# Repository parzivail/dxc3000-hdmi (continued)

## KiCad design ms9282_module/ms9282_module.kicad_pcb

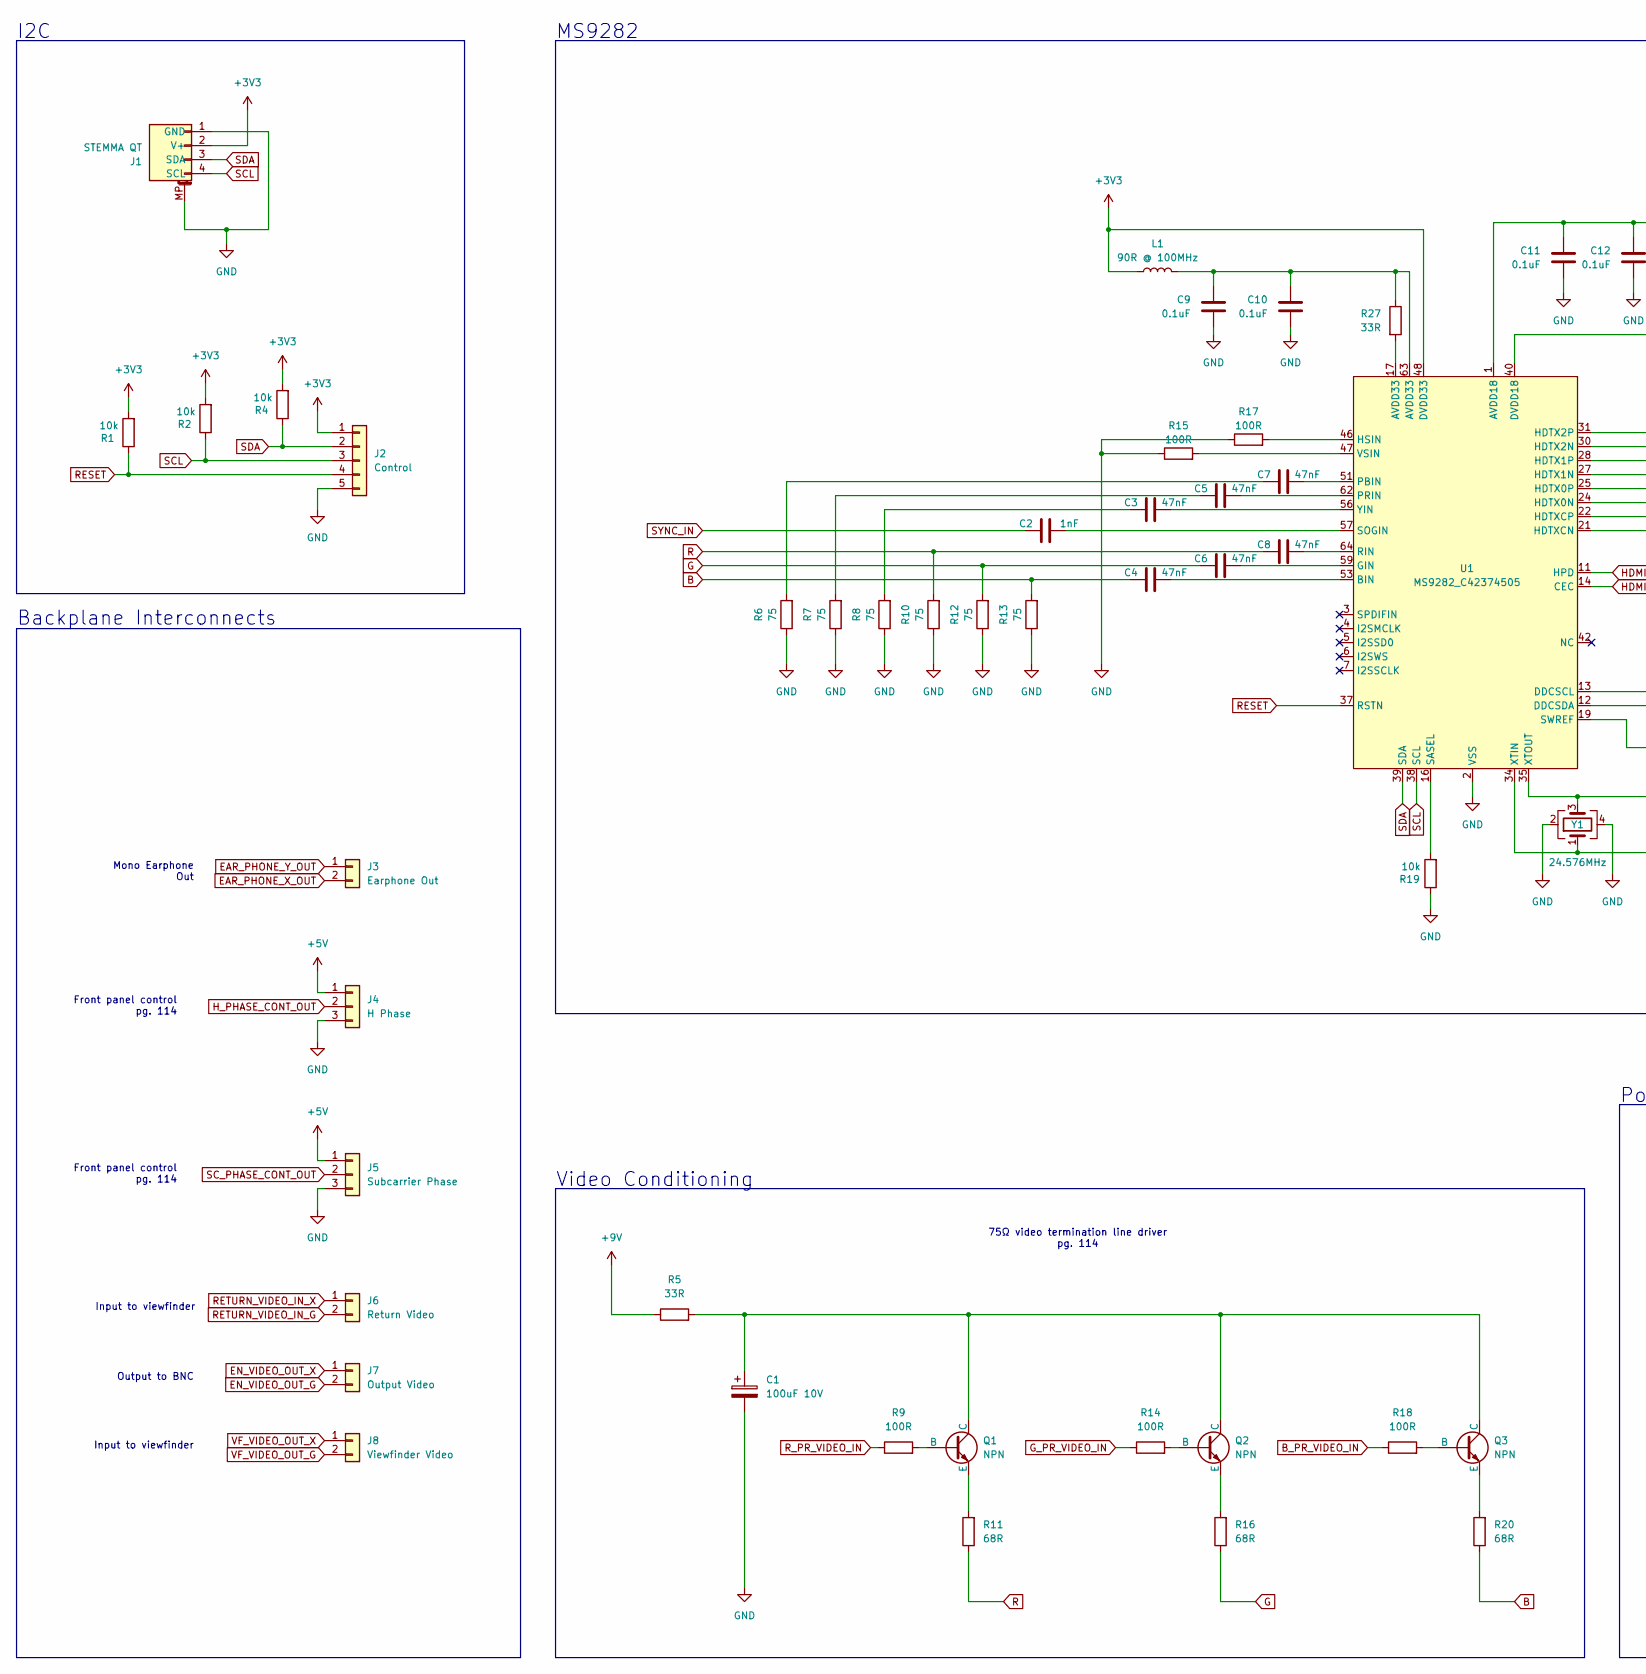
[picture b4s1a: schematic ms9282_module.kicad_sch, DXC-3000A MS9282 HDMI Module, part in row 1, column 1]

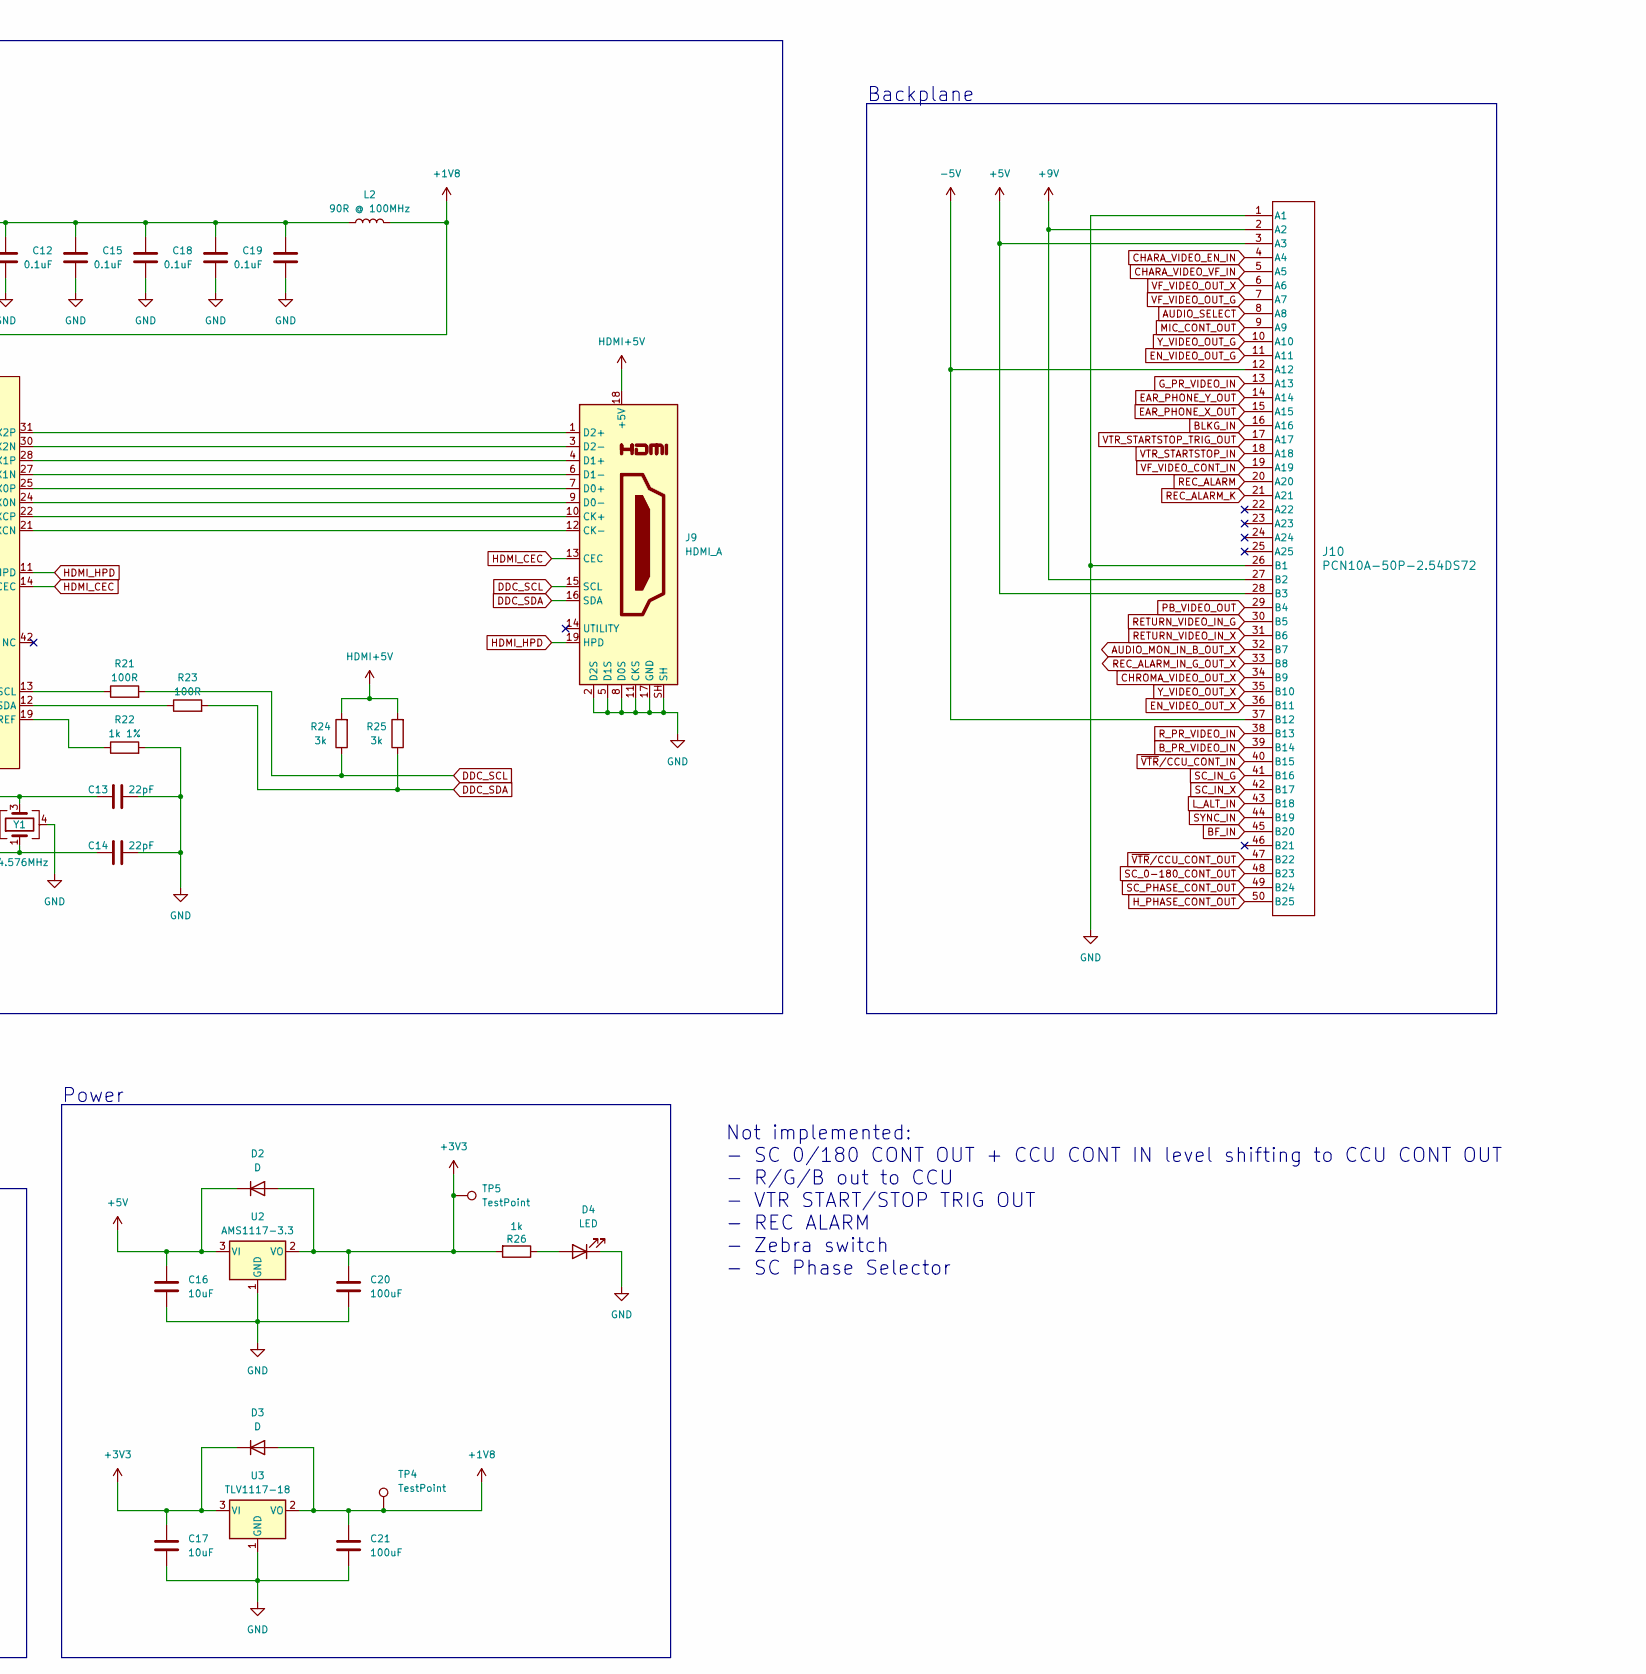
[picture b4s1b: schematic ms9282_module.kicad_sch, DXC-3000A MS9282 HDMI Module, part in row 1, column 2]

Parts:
C1: 100uF 10V; C_1206_3216Metric; LCSC Part C15008
C2: 1nF; C_0402_1005Metric; LCSC Part C1523
C3, C4, C5, C6, C7, C8: 47nF; C_0402_1005Metric; LCSC Part C307434
C9, C10, C11, C12, C15, C18, C19: 0.1uF; C_0402_1005Metric; LCSC Part C1525
C13, C14: 22pF; C_0402_1005Metric; LCSC Part C1555
C16, C17: 10uF; C_0402_1005Metric; LCSC Part C15525
C20, C21: 100uF; C_1206_3216Metric; LCSC Part C15008
D2, D3: D; D_SOD-123F; LCSC Part C64898
D4: LED; LED_0603_1608Metric; LCSC Part C2286
J1: STEMMA QT; JST_SH_SM04B-SRSS-TB_1x04-1MP_P1.00mm_Horizontal; LCSC Part C160404
J2: Control; PinHeader_1x05_P2.54mm_Horizontal
J3: Earphone Out; PinHeader_1x02_P2.54mm_Horizontal
J4: H Phase; PinHeader_1x03_P2.54mm_Horizontal
J5: Subcarrier Phase; PinHeader_1x03_P2.54mm_Horizontal
J6: Return Video; PinHeader_1x02_P2.54mm_Horizontal
J7: Output Video; PinHeader_1x02_P2.54mm_Horizontal
J8: Viewfinder Video; PinHeader_1x02_P2.54mm_Horizontal
J9: HDMI_A; HDMI_A_Molex_208658-1001_Horizontal; LCSC Part C2858275
J10: PCN10A-50P-2.54DS72; CONN_PCN10A-50P_HIR
L1, L2: 90R @ 100MHz; L_0805_2012Metric; LCSC Part C1015
Q1, Q2, Q3: NPN; SOT-23; LCSC Part C27829
R1, R2, R4, R19: 10k; R_0402_1005Metric; LCSC Part C25744
R5, R27: 33R; R_0402_1005Metric; LCSC Part C25105
R6, R7, R8, R10, R12, R13: 75; R_0402_1005Metric; LCSC Part C25133
R9, R14, R15, R17, R18, R21, R23: 100R; R_0402_1005Metric; LCSC Part C25076
R11, R16, R20: 68R; R_0603_1608Metric; LCSC Part C27592
R22: 1k 1%; R_0402_1005Metric; LCSC Part C11702
R24, R25: 3k; R_0402_1005Metric; LCSC Part C25890
R26: 1k; R_0402_1005Metric; LCSC Part C11702
TP4, TP5: TestPoint; TestPoint_Pad_D1.0mm
U1: MS9282_C42374505; LQFP-64_L10.0-W10.0-P0.50-LS12.0-BL; LCSC Part C42374505
U2: AMS1117-3.3; SOT-223-3_TabPin2; LCSC Part C6186
U3: TLV1117-18; SOT-223-3_TabPin2; LCSC Part C2862410
Y1: 24.576MHz; Crystal_SMD_3225-4Pin_3.2x2.5mm; LCSC Part C654993

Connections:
+1V8: C21.1, D3.2 (A), L2.2, TP4.1, U1.9 (DVDD18), U1.40 (DVDD18), U3.2 (VO)
+3V3: C17.1, C20.1, D2.2 (A), D3.1 (K), J1.2 (V+), J2.1, L1.1, R1.2, R2.2, R4.2, R26.2, TP5.1, U1.15 (DVDD33), U1.33 (DVDD33), U1.48 (DVDD33), U2.2 (VO), U3.3 (VI)
+5V: C16.1, D2.1 (K), J4.1, J5.1, J10.3 (A3), J10.28 (B3), U2.3 (VI)
+9V: J10.2 (A2), J10.27 (B2), R5.1
-5V: J10.12 (A12), J10.37 (B12)
AUDIO_MON_IN_B_OUT_X: J10.32 (B7)
AUDIO_SELECT: J10.8 (A8)
B: C4.2, R13.2, R20.1
BF_IN: J10.45 (B20)
BLKG_IN: J10.16 (A16)
B_PR_VIDEO_IN: J10.39 (B14), R18.1
CHARA_VIDEO_EN_IN: J10.4 (A4)
CHARA_VIDEO_VF_IN: J10.5 (A5)
CHROMA_VIDEO_OUT_X: J10.34 (B9)
DDC_SCL: J9.15 (SCL), R21.2, R24.1
DDC_SDA: J9.16 (SDA), R23.2, R25.1
EAR_PHONE_X_OUT: J3.2, J10.15 (A15)
EAR_PHONE_Y_OUT: J3.1, J10.14 (A14)
EN_VIDEO_OUT_G: J7.2, J10.11 (A11)
EN_VIDEO_OUT_X: J7.1, J10.36 (B11)
G: C6.2, R12.2, R16.1
GND: C1.2, C9.2, C10.2, C11.2, C12.2, C13.1, C14.1, C15.2, C16.2, C17.2, C18.2, C19.2, C20.2, C21.2, D4.1 (K), J1.1 (GND), J1.MP, J2.5, J4.3, J5.3, J9.2 (D2S), J9.5 (D1S), J9.8 (D0S), J9.11 (CKS), J9.17 (GND), J9.SH, J10.1 (A1), J10.26 (B1), R6.1, R7.1, R8.1, R10.1, R12.1, R13.1, R15.1, R17.1, R19.1, R22.2, U1.2 (VSS), U1.8 (VSS), U1.10 (VSS), U1.18 (VSS), U1.20 (VSS), U1.26 (VSS), U1.32 (VSS), U1.36 (VSS), U1.41 (VSS), U1.45 (VSS), U1.50 (VSS), U1.54 (VSS), U1.60 (VSS), U2.1 (GND), U3.1 (GND), Y1.2, Y1.4
G_PR_VIDEO_IN: J10.13 (A13), R14.1
HDMI+5V: J9.18 (+5V), R24.2, R25.2
HDMI_CEC: J9.13 (CEC), U1.14 (CEC)
HDMI_HPD: J9.19 (HPD), U1.11 (HPD)
H_PHASE_CONT_OUT: J4.2, J10.50 (B25)
L_ALT_IN: J10.43 (B18)
MIC_CONT_OUT: J10.9 (A9)
unnamed: C3.2, R8.2
unnamed: C5.2, R7.2
unnamed: C7.2, R6.2
unnamed: C9.1, C10.1, L1.2, R27.1, U1.49 (AVDD33), U1.52 (AVDD33), U1.58 (AVDD33), U1.63 (AVDD33)
unnamed: C11.1, C12.1, C15.1, C18.1, C19.1, L2.1, U1.1 (AVDD18), U1.23 (AVDD18), U1.29 (AVDD18), U1.55 (AVDD18), U1.61 (AVDD18)
unnamed: D4.2 (A), R26.1
unnamed: J9.10 (CK+), U1.22 (HDTXCP)
unnamed: J9.12 (CK-), U1.21 (HDTXCN)
unnamed: J9.7 (D0+), U1.25 (HDTX0P)
unnamed: J9.9 (D0-), U1.24 (HDTX0N)
unnamed: J9.4 (D1+), U1.28 (HDTX1P)
unnamed: J9.6 (D1-), U1.27 (HDTX1N)
unnamed: J9.1 (D2+), U1.31 (HDTX2P)
unnamed: J9.3 (D2-), U1.30 (HDTX2N)
unnamed: Q1.1 (B), R9.2
unnamed: C1.1, Q1.3 (C), Q2.3 (C), Q3.3 (C), R5.2
unnamed: Q1.2 (E), R11.2
unnamed: Q2.1 (B), R14.2
unnamed: Q2.2 (E), R16.2
unnamed: Q3.1 (B), R18.2
unnamed: Q3.2 (E), R20.2
unnamed: R27.2, U1.17 (AVDD33)
unnamed: C4.1, U1.53 (BIN)
unnamed: R21.1, U1.13 (DDCSCL)
unnamed: R23.1, U1.12 (DDCSDA)
unnamed: C6.1, U1.59 (GIN)
unnamed: R17.2, U1.46 (HSIN)
unnamed: C7.1, U1.51 (PBIN)
unnamed: C5.1, U1.62 (PRIN)
unnamed: C8.1, U1.64 (RIN)
unnamed: R19.2, U1.16 (SASEL)
unnamed: C2.1, U1.57 (SOGIN)
unnamed: R22.1, U1.19 (SWREF)
unnamed: R15.2, U1.47 (VSIN)
unnamed: C14.2, U1.34 (XTIN), Y1.1
unnamed: C13.2, U1.35 (XTOUT), Y1.3
unnamed: C3.1, U1.56 (YIN)
PB_VIDEO_OUT: J10.29 (B4)
R: C8.2, R10.2, R11.1
REC_ALARM: J10.20 (A20)
REC_ALARM_IN_G_OUT_X: J10.33 (B8)
REC_ALARM_K: J10.21 (A21)
RESET: J2.4, R1.1, U1.37 (RSTN)
RETURN_VIDEO_IN_G: J6.2, J10.30 (B5)
RETURN_VIDEO_IN_X: J6.1, J10.31 (B6)
R_PR_VIDEO_IN: J10.38 (B13), R9.1
SCL: J1.4 (SCL), J2.3, R2.1, U1.38 (SCL)
SC_0-180_CONT_OUT: J10.48 (B23)
SC_IN_G: J10.41 (B16)
SC_IN_X: J10.42 (B17)
SC_PHASE_CONT_OUT: J5.2, J10.49 (B24)
SDA: J1.3 (SDA), J2.2, R4.1, U1.39 (SDA)
SYNC_IN: C2.2, J10.44 (B19)
VF_VIDEO_CONT_IN: J10.19 (A19)
VF_VIDEO_OUT_G: J8.2, J10.7 (A7)
VF_VIDEO_OUT_X: J8.1, J10.6 (A6)
VTR_STARTSTOP_IN: J10.18 (A18)
VTR_STARTSTOP_TRIG_OUT: J10.17 (A17)
Y_VIDEO_OUT_G: J10.10 (A10)
Y_VIDEO_OUT_X: J10.35 (B10)
~VTR/CCU_CONT_IN: J10.40 (B15)
~VTR/CCU_CONT_OUT: J10.47 (B22)

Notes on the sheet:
75Ω video termination line driver pg. 114
Input to viewfinder
Front panel control pg. 114
MS9282
Backplane Interconnects
Video Conditioning
I2C
Power
Mono Earphone Out
Not implemented: - SC 0/180 CONT OUT + CCU CONT IN level shifting to CCU CONT OUT - R/G/B out to CCU - VTR START/STOP TRIG OUT - REC ALARM - Zebra switch - SC Phase Selector
Backplane
Output to BNC

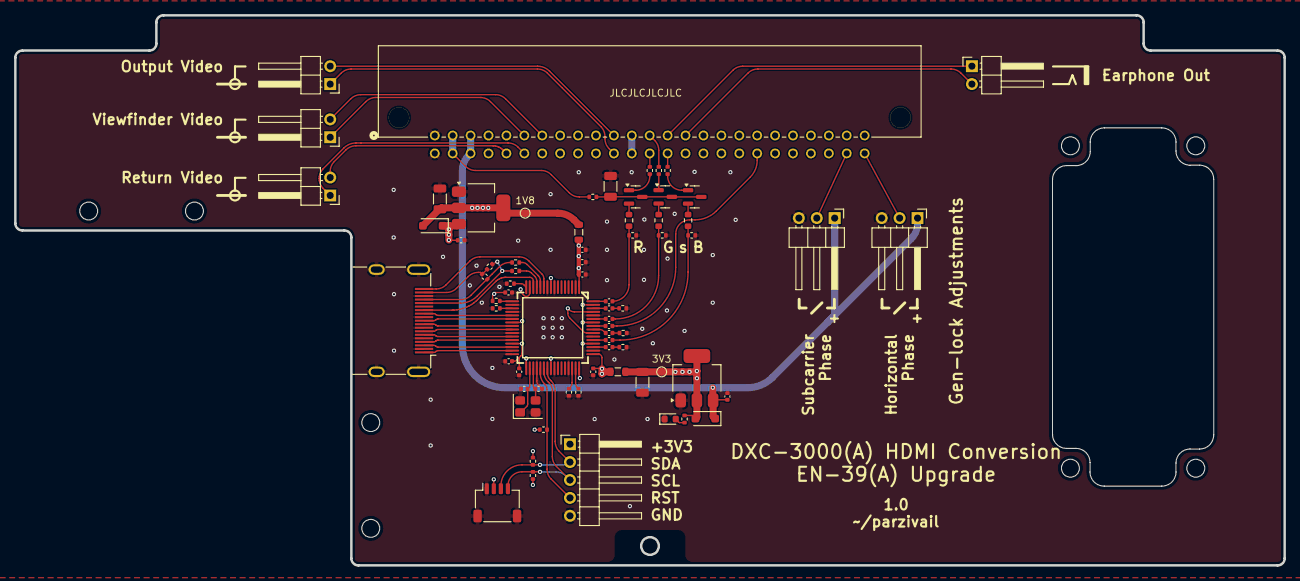
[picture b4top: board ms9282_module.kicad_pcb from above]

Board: 4 copper layers, 180.0 x 78.0 mm, 71 parts (0 on the bottom side), 68 nets.

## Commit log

2025-11-17 Add README
